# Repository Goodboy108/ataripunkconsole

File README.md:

# ataripunkconsole
This is a audio synth based on a NE556 IC dual timer. it uses 2 potentiometers to control the frequency and oscillation of the sound.
This project is made to recreate the tones atari retro games made and by rotating 2 knobs, you can alter the sound to how you want it!
motivation - I made this project because it is comparatively easier to make then other projects because this is my first ever hardware project. I also love the game console theme of it and also how it is not expensive to produce - what i thought. cause the pcb in my country is like 30$ gng, im cooked.

BOM--
https://docs.google.com/spreadsheets/d/1ZWKw14_xK2crBy8iU5RnvvLDdxu0tYG4yVFG7IDB0m0/edit?usp=sharing

pls go here 

PCB, https://jlcpcb.com/?_t=1777363531989&spm=jlcpcb.Public.2001&up_spm=Jlcpcb.Loginpage.1003, $30
Editor File-

https://cad.onshape.com/documents/c2ffda425c104f84df07931c/w/c49a1ccbf54cec41736d652f/e/a4275277b338c9575076d23b?renderMode=0&uiState=69f0734482d5808793d80294

assembly instruction- 

first, please solder all the components on to the pcb.
then solder the leads of the speakers to the pins on pcb. 
then solder the leads of the battery to the pins on the pcb. 
then put everything in the custom enclosure.

| Name | Unit | Price (INR) | Total Price (INR) | Link | Total (USD) | Notes |
|------|------|-------------|-------------------|------|-------------|-------|
| 14 Pin DIP IC Socket Base Adaptor | 3 | 4.61 | 13.83 | [Link](https://robu.in/product/14-pin-dip-ic-socket-base-adaptor-pack-of-5) | 0.15 |  |
| 10nF (0.01uF - 2E103J) - 250V Polyester Film Capacitor | 4 | 3.17 | 12.68 | [Link](https://robu.in/product/10nf-0-01uf-2e103j-250v-polyester-film-capacitor-pack-of-10) | 0.13 | cheapest in the UAE |
| 100nF 400V DIP Polyester Film Capacitor | 3 | 4.67 | 14.01 | [Link](https://robu.in/product/100nf-400v-dip-polyester-film-capacitor-pitch10mm) | 0.15 |  |
| 0.5W 28mm 8Ω Trumpet Speaker Mini Audio Buzzer Driver | 2 | 10 | 20 | [Link](https://robu.in/product/0-5w-8ohm-trumpet-speaker-diameter-28mm) | 0.21 |  |
| 4mm SPDT 1P2T Slide Switch | 3 | 4 | 12 | [Link](https://robu.in/product/4mm-spdt-1p2t-slide-switch-pack-of-10) | 0.13 |  |
| I Type 9V Battery Connector Cable | 2 | 28 | 56 | [Link](https://robu.in/product/i-type-9v-battery-connector-buckle-with-dc15cm-black-and-red-cable) | 0.59 |  |
| NE556N IC - Dual Timer IC | 2 | 23 | 46 | [Link](https://robu.in/product/ne556n-ic-dual-timer-ic) | 0.49 |  |
| 1kΩ Resistor (CFR-25JB-52) | 7 | 1.56 | 10.92 | [Link](https://robu.in/product/cfr-25jb-52-1k-yageo-through-hole-resistor-1-kohm-cfr-series-250-mw-%c2%b1-5-axial-leaded-250-v) | 0.12 |  |
| 500kΩ Trimming Potentiometer | 3 | 36 | 108 | [Link](https://robu.in/product/500-kohm-500-mw-10-through-hole-pcb-bourns-trimming-potentiometer) | 1.14 |  |
| 470Ω Resistor (CFR-50JT-52) | 10 | 1.47 | 14.7 | [Link](https://robu.in/product/cfr-50jt-52-470r-yageo-through-hole-resistor-470-ohm-cfr-series-500-mw-%c2%b1-5-axial-leaded-350-v) | 0.16 |  |
| PCB (JLCPCB) | 5 | 75.72 | 378.6 | [Link](https://cart.jlcpcb.com/shopcart/cart) | 4.00 |  |

**Total Cost (INR):** 752.51  
**Total Cost (USD):** 7.95  
**Shipping:** $27.57

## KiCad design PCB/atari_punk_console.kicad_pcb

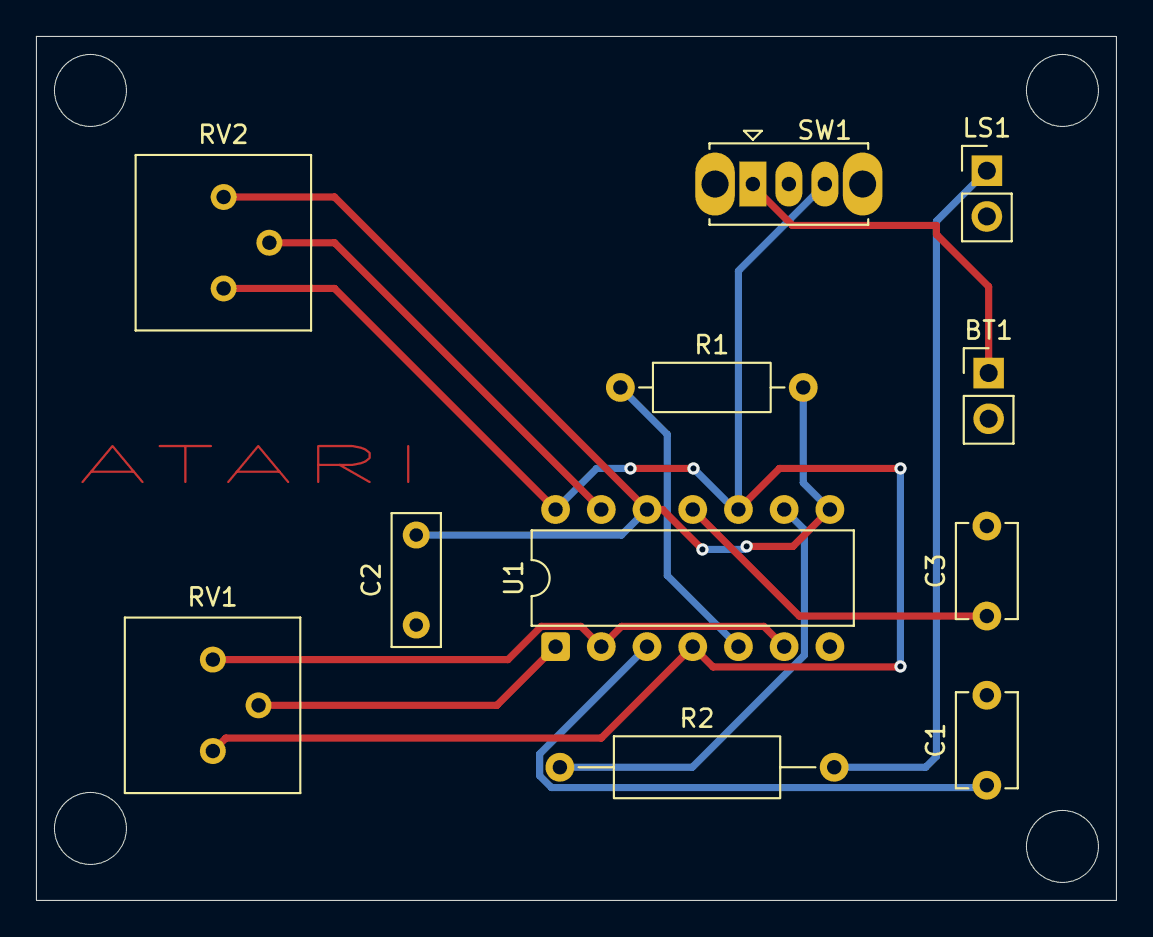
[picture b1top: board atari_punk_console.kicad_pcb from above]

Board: 4 copper layers, 60.0 x 48.0 mm, 11 parts (0 on the bottom side), 12 nets.

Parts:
BT1: Battery_Cell; PinHeader_1x02_P2.54mm_Vertical
C1, C3: 10nF; C_Disc_D5.1mm_W3.2mm_P5.00mm
C2: 100nF; C_Rect_L7.2mm_W2.5mm_P5.00mm
LS1: Speaker; PinHeader_1x02_P2.54mm_Vertical
R1: 1k; R_Axial_DIN0207_L6.3mm_D2.5mm_P10.16mm_Horizontal
R2: 470; R_Axial_DIN0309_L9.0mm_D3.2mm_P15.24mm_Horizontal
RV1, RV2: R_Potentiometer_Trim 500k; Potentiometer_Bourns_3386P_Vertical
SW1: SW_SPDT; SW_Slide_SPDT_Straight_CK_OS102011MS2Q
U1: NE556; DIP-14_W7.62mm

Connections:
GND: BT1.2 (-), C1.2, C2.1, C3.2, LS1.2, U1.7 (GND)
unnamed: BT1.1 (+), SW1.1 (A)
unnamed: LS1.1, R2.2
unnamed: C1.1, U1.3 (CONT)
unnamed: RV1.2, U1.1 (DISCH)
unnamed: R1.1, U1.5 (OUT)
unnamed: RV1.3, U1.2 (THRES), U1.6 (TRIG)
unnamed: C3.1, U1.11 (CONT)
unnamed: RV2.2, U1.13 (DISCH)
unnamed: R2.1, U1.9 (OUT)
unnamed: C2.2, R1.2, RV2.3, U1.8 (TRIG), U1.12 (THRES)
VCC: RV1.1, RV2.1, SW1.3 (C), U1.4 (~RST), U1.10 (~RST), U1.14 (VCC)

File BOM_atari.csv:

Name ,Unit,Price (INR),Total Price (INR),Link,Total (USD),Total,Total (USD),Shipping 
14 Pin DIP IC Socket Base Adaptor,3,4.61,13.83,https://robu.in/product/14-pin-dip-ic-socket-base-adaptor-pack-of-5,0.15,752.51,7.95,$27.57
10nF (0.01uF - 2E103J) - 250V Polyester Film Capacitor,4,3.17,12.68,https://robu.in/product/10nf-0-01uf-2e103j-250v-polyester-fi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,0.13,,,its expensive in the uae
100nF 400V DIP Polyester Film Capacitor,3,4.67,14.01,https://robu.in/product/100nf-400v-dip-polyester-film-capaci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,0.15,,,
0.5W 28mm 8Ω Trumpet Speaker Mini Audio Buzzer Driver,2,10,20,https://robu.in/product/0-5w-8ohm-trumpet-speaker-diameter-28mm,0.21,,,
4mm SPDT 1P2T Slide Switch,3,4,12,https://robu.in/product/4mm-spdt-1p2t-slide-switch-pack-of-10,0.13,,,
"I Type 9V Battery, Clips Connector, Buckle with DC15CM, Black and Red Cable",2,28,56, https://robu.in/product/i-type-9v-battery-connector-buckle-w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,0.59,,,
NE556N IC - Dual Timer IC,2,23,46,https://robu.in/product/ne556n-ic-dual-timer-ic,0.49,,,
"CFR-25JB-52-1K-YAGEO-Through Hole Resistor, 1 kohm, CFR Series, 250 mW, ± 5%, Axial Leaded, 250 V",7,1.56,10.92,https://robu.in/product/cfr-25jb-52-1k-yageo-through-hole-re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,0.12,,,
"500 kohm 500 mW 10 % Through Hole , PCB Bourns Trimming Potentiometer",3,36,108,https://robu.in/product/500-kohm-500-mw-10-through-hole-pcb-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,1.14,,,
"CFR-50JT-52-470R-YAGEO-Through Hole Resistor, 470 ohm, CFR Series, 500 mW, ± 5%, Axial Leaded, 350 V",10,1.47,14.7,https://robu.in/product/cfr-50jt-52-470r-yageo-through-hole-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,0.16,,,
PCB(JLCPCB),5,75.72,378.6,https://cart.jlcpcb.com/shopcart/cart,4,,,

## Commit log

2026-04-29 Create cad
2026-04-29 Create pcb
2026-04-29 Create production
